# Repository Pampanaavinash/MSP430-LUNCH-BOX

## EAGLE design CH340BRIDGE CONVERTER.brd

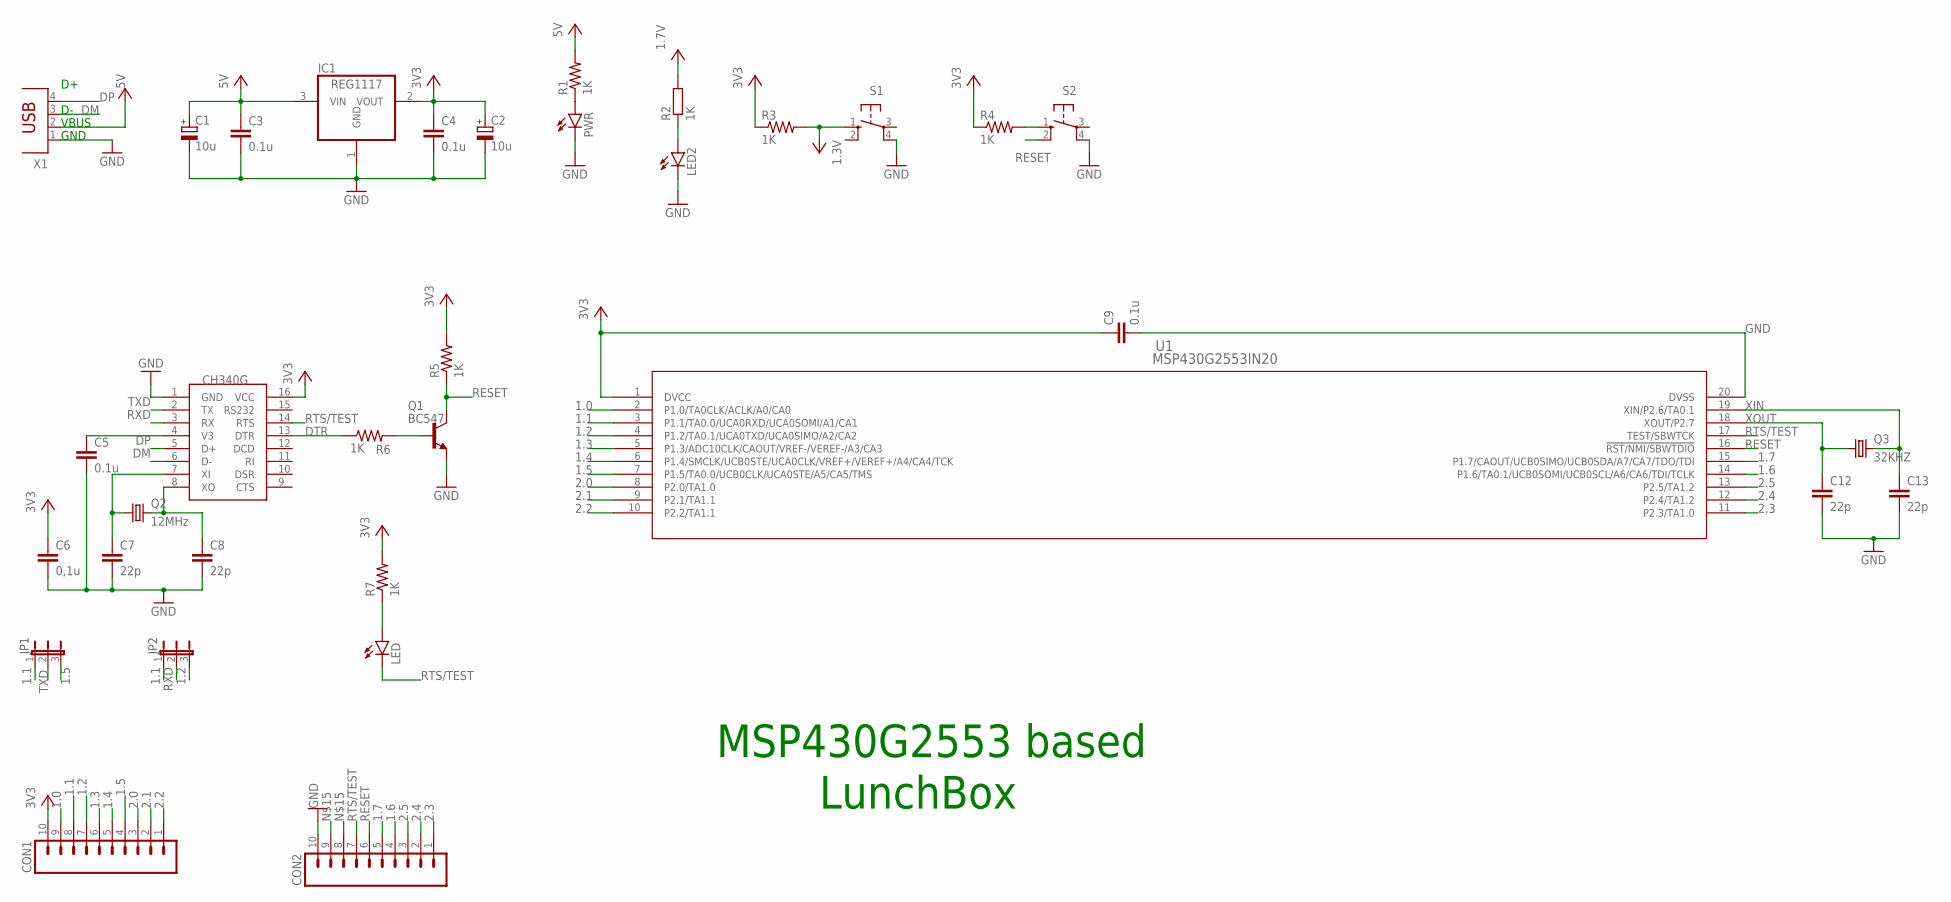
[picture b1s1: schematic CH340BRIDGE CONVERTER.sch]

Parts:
C1, C2: 10u; TT5D7
C3, C4: 0.1u; C025-025X050
C5: 0.1u; C0805
C6: 0,1u; C0805
C7, C8, C12, C13: 22p; C0805
C9: 0.1u; C075-032X103
CON1, CON2: M10; 10P
IC1: REG1117; SOT223
JP1, JP2: JP2E; JP2
LED, LED2: LED3MM
PWR: LED3MM
Q1: BC547; TO92
Q2: 12MHz; HC49/S
Q3: 32KHZ; TC26H
R1, R5, R6, R7: 1K; 0207/10
R2: 1K; 0207/12
R3, R4: 1K; 0204/7
S1, S2: 10-XX; B3F-10XX
U1: MSP430G2553IN20; N20_TEX
U$1: CH340G; SOIC16
X1: PN87520

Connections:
1.0: CON1.9, U1.2 (P1.0/TA0CLK/ACLK/A0/CA0)
1.1: CON1.8, JP1.1, JP2.1, U1.3 (P1.1/TA0.0/UCA0RXD/UCA0SOMI/A1/CA1)
1.2: CON1.7, JP2.3, U1.4 (P1.2/TA0.1/UCA0TXD/UCA0SIMO/A2/CA2)
1.3: CON1.6, U1.5 (P1.3/ADC10CLK/CAOUT/VREF-/VEREF-/A3/CA3)
1.4: CON1.5, U1.6 (P1.4/SMCLK/UCB0STE/UCA0CLK/VREF+/VEREF+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)
1.5: CON1.4, JP1.3, U1.7 (P1.5/TA0.0/UCB0CLK/UCA0STE/A5/CA5/TMS)
1.6: CON2.4, U1.14 (P1.6/TA0.1/UCB0SOMI/UCB0SCL/A6/CA6/TDI/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)
1.7: CON2.5, U1.15 (P1.7/CAOUT/UCB0SIMO/UCB0SDA/A7/CA7/TDO/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)
2.0: CON1.3, U1.8 (P2.0/TA1.0)
2.1: CON1.2, U1.9 (P2.1/TA1.1)
2.2: CON1.1, U1.10 (P2.2/TA1.1)
2.3: CON2.1, U1.11 (P2.3/TA1.0)
2.4: CON2.2, U1.12 (P2.4/TA1.2)
2.5: CON2.3, U1.13 (P2.5/TA1.2)
DM: U$1.6 (D-), X1.3
DP: U$1.5 (D+), X1.4
DTR: R6.1, U$1.13 (DTR)
GND: C1.-, C2.-, C3.2, C4.2, C5.2, C6.2, C7.2, C8.2, C9.2, C12.2, C13.2, CON2.10, IC1.1 (GND), LED2.K (C), PWR.K (C), Q1.1 (E), S1.4 (P1), S2.4 (P1), U1.20 (DVSS), U$1.1 (GND), X1.1
unnamed: PWR.A, R1.1
unnamed: LED2.A, R2.1
unnamed: R4.2, S2.1 (S)
unnamed: C5.1, U$1.4 (V3)
unnamed: C7.1, Q2.1, U$1.7 (XI)
unnamed: C8.1, Q2.2, U$1.8 (XO)
unnamed: Q1.2 (B), R6.2
unnamed: LED.A, R7.1
unnamed: CON2.8, CON2.9
RESET: CON2.6, Q1.3 (C), R5.1, S2.2 (S1), U1.16 (!RST/NMI/SBWTDIO)
RTS/TEST: CON2.7, LED.K (C), U1.17 (TEST/SBWTCK), U$1.14 (RTS)
RXD: JP2.2, U$1.3 (RX)
TXD: JP1.2, U$1.2 (TX)
VCC: C1.+, C2.+, C3.1, C4.1, C6.1, C9.1, CON1.10, IC1.2 (VOUT), IC1.3 (VIN), R1.2, R2.2, R3.1, R3.2, R4.1, R5.2, R7.2, S1.1 (S), U1.1 (DVCC), U$1.16 (VCC), X1.2
XIN: C13.1, Q3.2, U1.19 (XIN/P2.6/TA0.1)
XOUT: C12.1, Q3.1, U1.18 (XOUT/P2.7)

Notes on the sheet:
VBUS
GND
MSP430G2553 based
LunchBox

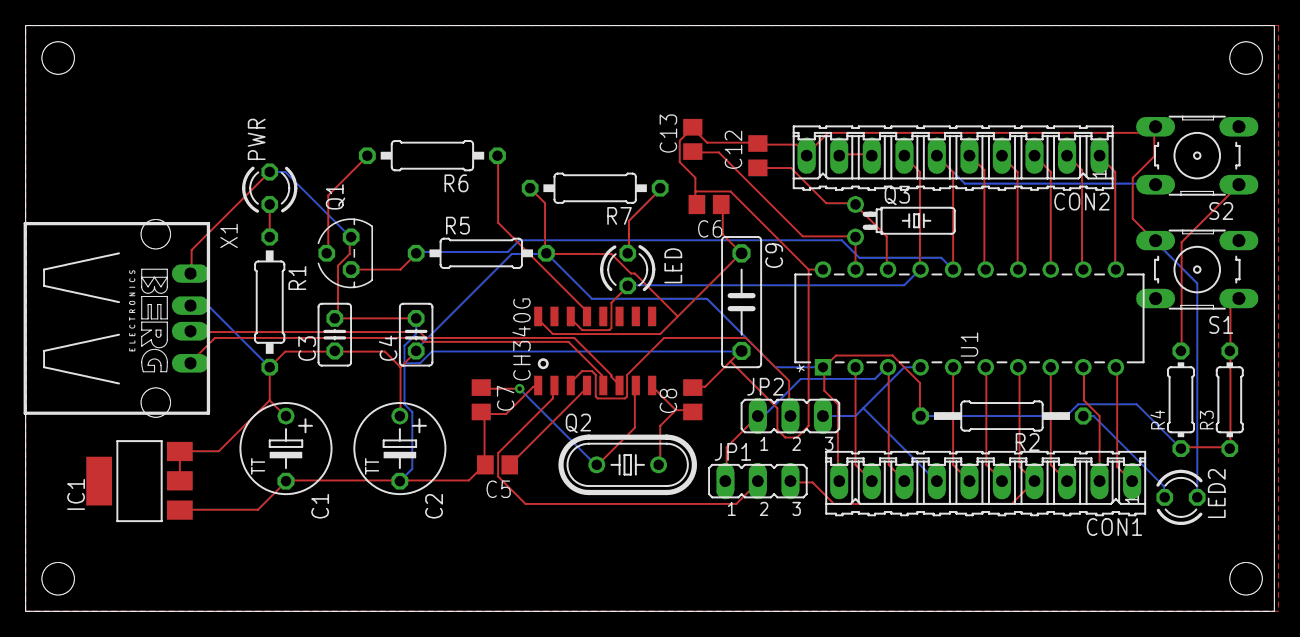
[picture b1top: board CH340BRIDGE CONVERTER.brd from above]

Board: 2 copper layers, 97.5 x 45.7 mm, 34 parts (0 on the bottom side), 34 nets.

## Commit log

2025-01-01 Create hardware
2025-01-01 Create Libraries

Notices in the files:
parts and their libraries:
COPYRIGHT: Copyright (C) 2024 Ultra Librarian. All rights reserved.
